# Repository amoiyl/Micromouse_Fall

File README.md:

# Micromouse Fall 2023 Syllabus
- - - - - - - - - - - - - - - - - - - <br />

Competed in IEEE @ UCLA's Fall Micromouse Rat Competition!! <br />

# Design: <br />
  -- Power Delivery Schematic <br />
  -- Power Delivery PCB <br />
  -- H-Bridge <br />
  -- IR Emitters and Receivers <br />

# Code: <br />
  -- move(1) in main.c traverses the length of one maze unit <br />
  -- turn(1) in main.c rotates 90 degrees in place <br />
  -- usage of the IR functionality yield an autonomous maze solving robot (rat) !! <br />

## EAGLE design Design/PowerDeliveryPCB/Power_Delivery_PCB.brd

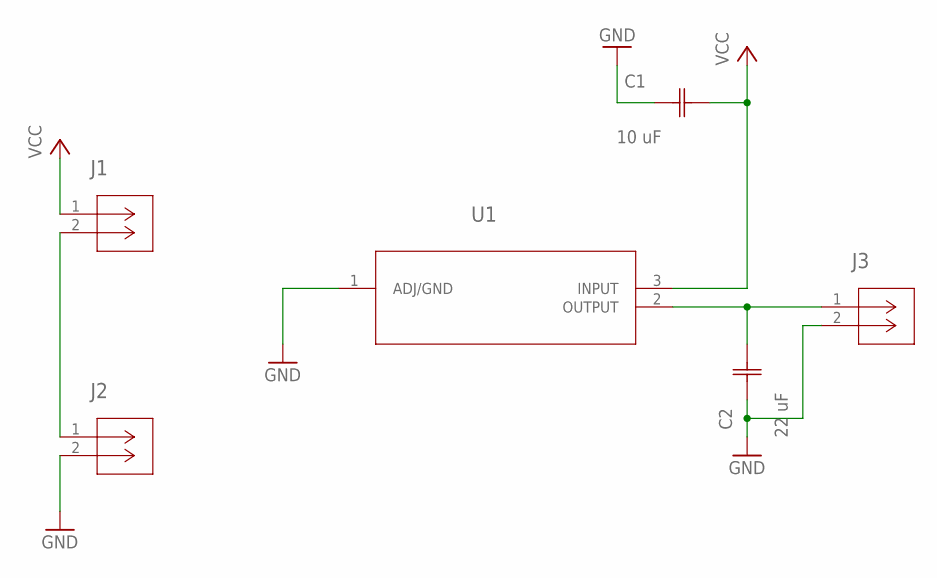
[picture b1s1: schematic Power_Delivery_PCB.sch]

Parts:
C1: 10 uF; G-21_MUR-L
C2: 22 uF; G-188_MUR-L
J1, J2, J3: B2B-PH-K-S(LF)(SN)CONN_B2B-PH-K-S(LF)(SN)_JST; CONN_B2B-PH-K-S(LF)(SN)_JST
U1: AZ1117IH-3.3TRG1SOT223_AZ1117I_6P5X3P5_DIO-L; SOT223_AZ1117I_6P5X3P5_DIO-L

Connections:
GND: C1.1, C2.1, J2.2, J3.2, U1.1 (ADJ/GND)
unnamed: J1.2, J2.1
unnamed: C2.2, J3.1, U1.2 (OUTPUT)
VCC: C1.2, J1.1, U1.3 (INPUT)

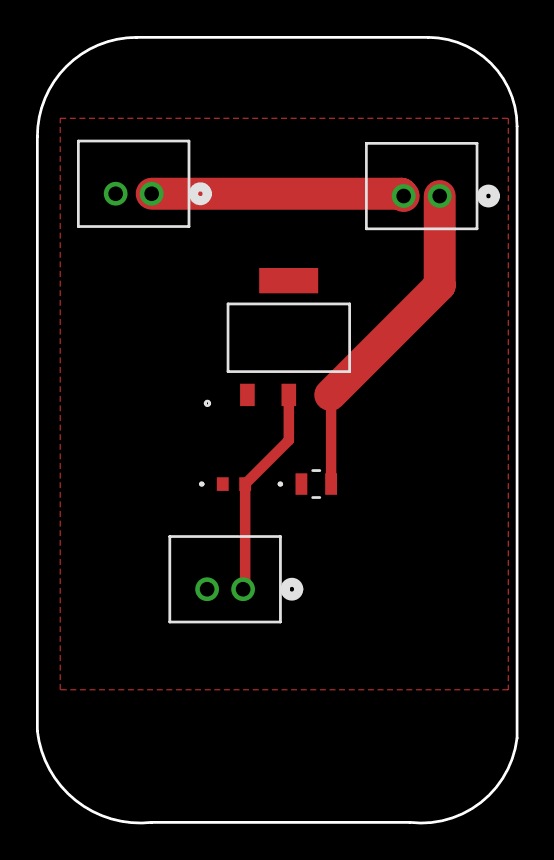
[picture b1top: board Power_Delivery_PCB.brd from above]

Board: 2 copper layers, 26.6 x 43.6 mm, 6 parts (0 on the bottom side), 4 nets.

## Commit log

2023-11-05 11/04/2023
    assignment 2a incomplete
2023-11-05 -pwm fix
2023-11-06 assignment 2a checked off
2023-11-27 straight pid
2023-11-28 turn and move not working
2023-12-03 pls work
2023-12-05 working
2023-12-06 rename
2023-12-21 Completed Rat Design
2023-12-21 code files
2023-12-21 project clean
2024-01-05 fully functioning

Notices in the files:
parts and their libraries:
COPYRIGHT: Copyright (C) 2023 Ultra Librarian. All rights reserved.
